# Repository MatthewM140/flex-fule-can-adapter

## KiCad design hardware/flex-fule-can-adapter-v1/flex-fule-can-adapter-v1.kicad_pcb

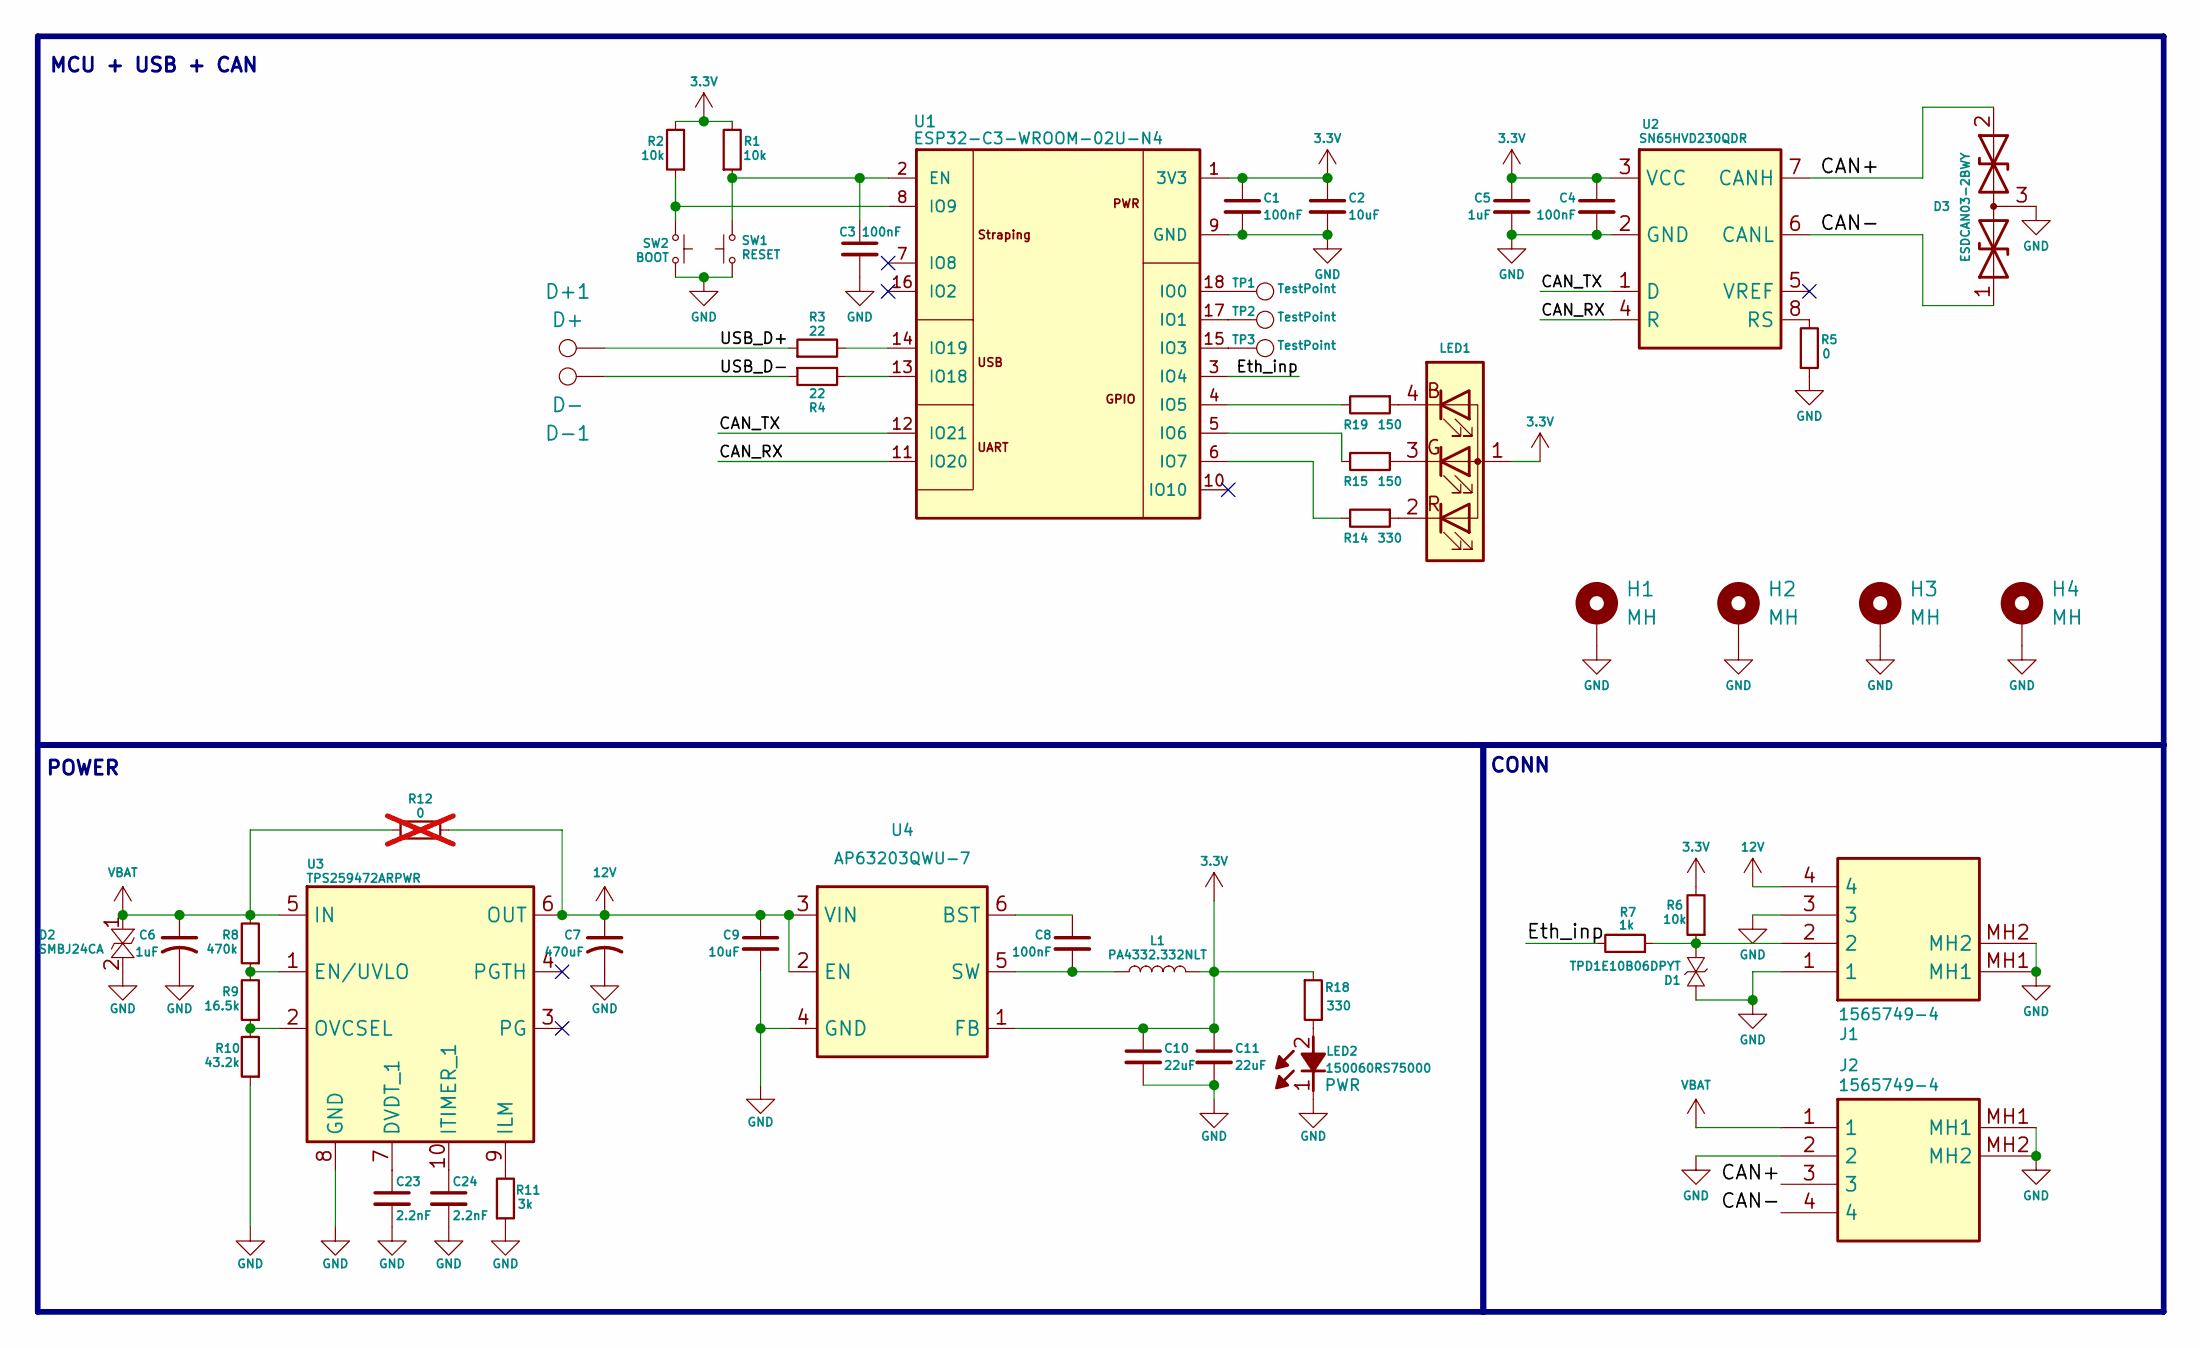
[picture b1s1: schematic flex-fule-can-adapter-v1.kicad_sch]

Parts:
C1, C3, C4, C8: 100nF; C_0603_1608Metric_Pad1.08x0.95mm_HandSolder
C2, C9: 10uF; C_0603_1608Metric_Pad1.08x0.95mm_HandSolder
C5, C6: 1uF; C_0603_1608Metric_Pad1.08x0.95mm_HandSolder
C7: 470uF; C_0603_1608Metric_Pad1.08x0.95mm_HandSolder
C10, C11: 22uF; C_0603_1608Metric_Pad1.08x0.95mm_HandSolder
C23, C24: 2.2nF; C_0603_1608Metric
D1: TPD1E10B06DPYT; DIO_TPD1E05U06DPYR
D2: SMBJ24CA; DIOM5436X244N; Mouser Part Number 576-SMBJ24CA
D3: ESDCAN03-2BWY; SOT65P210X110-3N; Mouser Part Number 511-ESDCAN03-2BWY
D+1: D+; TestPoint_Pad_D2.0mm
D-1: D-; TestPoint_Pad_D2.0mm
H1, H2, H3, H4: MH; MountingHole_2.2mm_M2_Pad_Via
J1, J2: 1565749-4; 15657494; Mouser Part Number 571-1565749-4
L1: PA4332.332NLT; PA4332332NLT; Mouser Part Number 673-PA4332332NLT
LED1: CLMUD-FKC-CHJNPM569ABB845343; PLCC4_CLMUD-FKC_CRW-L
LED2: 150060RS75000; LEDC1608X80N; Mouser Part Number 710-150060RS75000
R1, R2, R6: 10k; R_0603_1608Metric_Pad0.98x0.95mm_HandSolder
R3, R4: 22; R_0603_1608Metric_Pad0.98x0.95mm_HandSolder
R5: 0; R_0603_1608Metric_Pad0.98x0.95mm_HandSolder
R7: 1k; R_0603_1608Metric_Pad0.98x0.95mm_HandSolder
R8: 470k; R_0603_1608Metric_Pad0.98x0.95mm_HandSolder
R9: 16.5k; R_0603_1608Metric_Pad0.98x0.95mm_HandSolder
R10: 43.2k; R_0603_1608Metric_Pad0.98x0.95mm_HandSolder
R11: 3k; R_0603_1608Metric_Pad0.98x0.95mm_HandSolder
R12: 0; R_0603_1608Metric_Pad0.98x0.95mm_HandSolder; not fitted
R14: 330; R_0603_1608Metric_Pad0.98x0.95mm_HandSolder
R15, R19: 150; R_0603_1608Metric_Pad0.98x0.95mm_HandSolder
R18: 330; R_0603_1608Metric
SW1: RESET; SW_SPST_CK_RS282G05A3
SW2: BOOT; SW_SPST_CK_RS282G05A3
TP1, TP2, TP3: TestPoint; TestPoint_Pad_D1.5mm
U1: ESP32-C3-WROOM-02U-N4; XCVR_ESP32-C3-WROOM-02U-N4; PARTREV 1.3
U2: SN65HVD230QDR; SOIC127P600X175-8N; Mouser Part Number 595-SN65HVD230QDR
U3: TPS259472ARPWR; Mouser Part Number 595-TPS259472ARPWR
U4: AP63203QWU-7; SOT95P280X100-6N; Mouser Part Number 621-AP63203QWU-7

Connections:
3.3V: C1.1, C2.1, C4.1, C5.1, C10.1, C11.1, L1.2, LED1.1 (A), R1.2, R2.2, R6.2, R18.1, U1.1 (3V3), U2.3 (VCC), U4.1 (FB)
12V: C7.1, C9.1, J1.4, R12.2, U3.6 (OUT), U4.2 (EN), U4.3 (VIN)
/CAN+: D3.2, J2.3, U2.7 (CANH)
/CAN-: D3.1, J2.4, U2.6 (CANL)
/CAN_RX: U1.11 (IO20), U2.4 (R)
/CAN_TX: U1.12 (IO21), U2.1 (D)
/Eth_inp: R7.2, U1.3 (IO4)
/USB_D+: D+1.1, R3.1; also elsewhere on the board
/USB_D-: D-1.1, R4.1; also elsewhere on the board
GND: C1.2, C2.2, C3.2, C4.2, C5.2, C6.2, C7.2, C9.2, C10.2, C11.2, C23.2, C24.2, D1.1, D2.2, D3.3, H1.1 (1_1), H2.1 (1_1), H3.1 (1_1), H4.1 (1_1), J1.1, J1.3, J1.MH1, J1.MH2, J2.2, J2.MH1, J2.MH2, LED2.1 (K), R5.1, R10.1, R11.1, SW1.1, SW2.1, U1.9 (GND), U1.19_1 (GND__1), U1.19_2 (GND__2), U1.19_3 (GND__3), U1.19_4 (GND__4), U1.19_5 (GND__5), U1.19_6 (GND__6), U1.19_7 (GND__7), U1.19_8 (GND__8), U1.19_9 (GND__9), U2.2 (GND), U3.8 (GND), U4.4 (GND)
unnamed: D1.2, J1.2, R6.1, R7.1
unnamed: LED1.4 (B), R19.1
unnamed: LED1.3 (G), R15.1
unnamed: LED1.2 (R), R14.1
unnamed: LED2.2 (A), R18.2
unnamed: C3.1, R1.1, SW1.2, U1.2 (EN)
unnamed: TP1.1 (1_1), U1.18 (IO0)
unnamed: TP2.1 (1_1), U1.17 (IO1)
unnamed: TP3.1 (1_1), U1.15 (IO3)
unnamed: R19.2, U1.4 (IO5)
unnamed: R15.2, U1.5 (IO6)
unnamed: R14.2, U1.6 (IO7)
unnamed: R2.1, SW2.2, U1.8 (IO9)
unnamed: R4.2, U1.13 (IO18)
unnamed: R3.2, U1.14 (IO19)
unnamed: R5.2, U2.8 (RS)
unnamed: C23.1, U3.7 (DVDT_1), U3.14 (DVDT_2)
unnamed: R8.1, R9.2, U3.1 (EN/UVLO), U3.12 (EN/UVLO_2)
unnamed: R11.2, U3.9 (ILM)
unnamed: C24.1, U3.10 (ITIMER_1), U3.11 (ITIMER_2)
unnamed: R9.1, R10.2, U3.2 (OVCSEL)
unnamed: C8.1, U4.6 (BST)
unnamed: C8.2, L1.1, U4.5 (SW)
VBAT: C6.1, D2.1, J2.1, R8.2, R12.1, U3.5 (IN)

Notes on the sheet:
POWER
CONN
MCU + USB + CAN

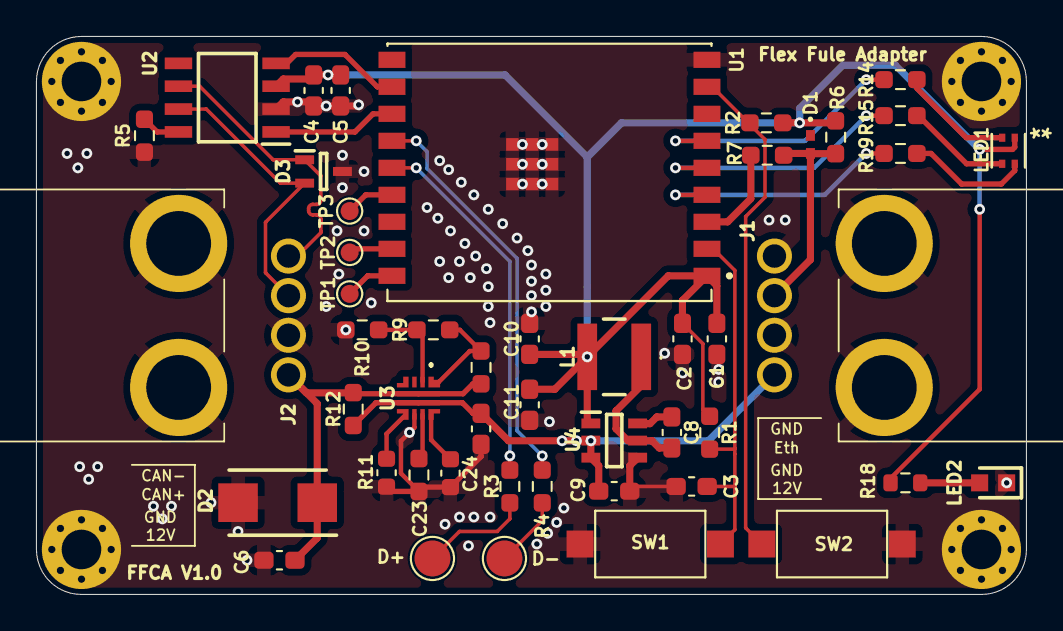
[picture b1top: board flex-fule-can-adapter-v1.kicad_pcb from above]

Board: 2 copper layers, 55.0 x 31.0 mm, 52 parts (0 on the bottom side), 34 nets.

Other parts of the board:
D+: D+; TestPoint_Pad_D2.0mm
D-: D-; TestPoint_Pad_D2.0mm

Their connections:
/USB_D+: D+.1 (1_1); also elsewhere on the board
/USB_D-: D-.1 (1_1); also elsewhere on the board
